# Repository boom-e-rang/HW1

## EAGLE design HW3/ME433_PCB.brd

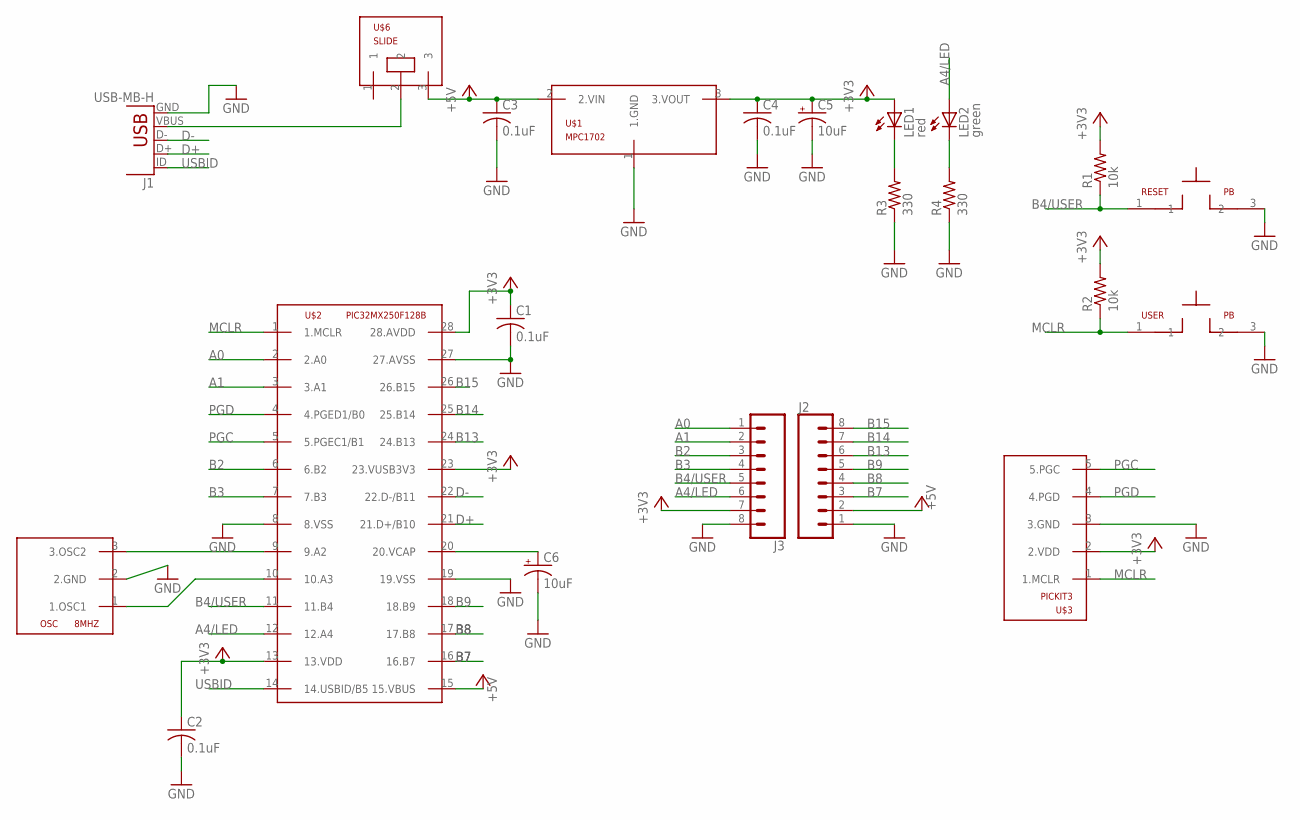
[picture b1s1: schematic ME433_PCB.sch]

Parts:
8MHZ: OSC
C1, C2, C3, C4: 0.1uF; C025-025X050
C5, C6: 10uF; B45181B
J1: USB-MB-H
J2, J3: CONN_08"; 1X08
LED1: red; LED3MM
LED2: green; LED3MM
R1, R2: 10k; 0207/10
R3, R4: 330; 0207/10
RESET: PB
U$1: MPC1702; TO92
U$2: PIC32MX250F128B; DIL28-3
U$3: PICKIT3; 1X05
U$6: SLIDE
USER: PB

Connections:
+3V3: C1.1, C2.1, C4.1, C5.+, J3.7, LED1.A, R1.2, R2.2, U$1.3 (3.VOUT), U$2.13 (13.VDD), U$2.23 (23.VUSB3V3), U$2.28 (28.AVDD), U$3.2 (2.VDD)
+5V: C3.1, J2.2, U$1.2 (2.VIN), U$2.15 (15.VBUS), U$6.3
A0: J3.1, U$2.2 (2.A0)
A1: J3.2, U$2.3 (3.A1)
A4/LED: J3.6, LED2.A, U$2.12 (12.A4)
B2: J3.3, U$2.6 (6.B2)
B3: J3.4, U$2.7 (7.B3)
B4/USER: J3.5, R1.1, RESET.1, U$2.11 (11.B4)
B7: J2.3, U$2.16 (16.B7)
B8: J2.4, U$2.17 (17.B8)
B9: J2.5, U$2.18 (18.B9)
B13: J2.6, U$2.24 (24.B13)
B14: J2.7, U$2.25 (25.B14)
B15: J2.8, U$2.26 (26.B15)
D+: J1.D+, U$2.21 (21.D+/B10)
D-: J1.D-, U$2.22 (22.D-/B11)
GND: 8MHZ.2 (2.GND), C1.2, C2.2, C3.2, C4.2, C5.-, C6.-, J1.GND, J2.1, J3.8, R3.1, R4.1, RESET.3 (2), U$1.1 (1.GND), U$2.8 (8.VSS), U$2.19 (19.VSS), U$2.27 (27.AVSS), U$3.3 (3.GND), USER.3 (2)
MCLR: R2.1, U$2.1 (1.MCLR), U$3.1 (1.MCLR), USER.1
unnamed: J1.VBUS, U$6.2
unnamed: 8MHZ.3 (3.OSC2), U$2.9 (9.A2)
unnamed: LED1.K (C), R3.2
unnamed: LED2.K (C), R4.2
unnamed: C6.+, U$2.20 (20.VCAP)
unnamed: 8MHZ.1 (1.OSC1), U$2.10 (10.A3)
PGC: U$2.5 (5.PGEC1/B1), U$3.5 (5.PGC)
PGD: U$2.4 (4.PGED1/B0), U$3.4 (4.PGD)
USBID: J1.ID, U$2.14 (14.USBID/B5)

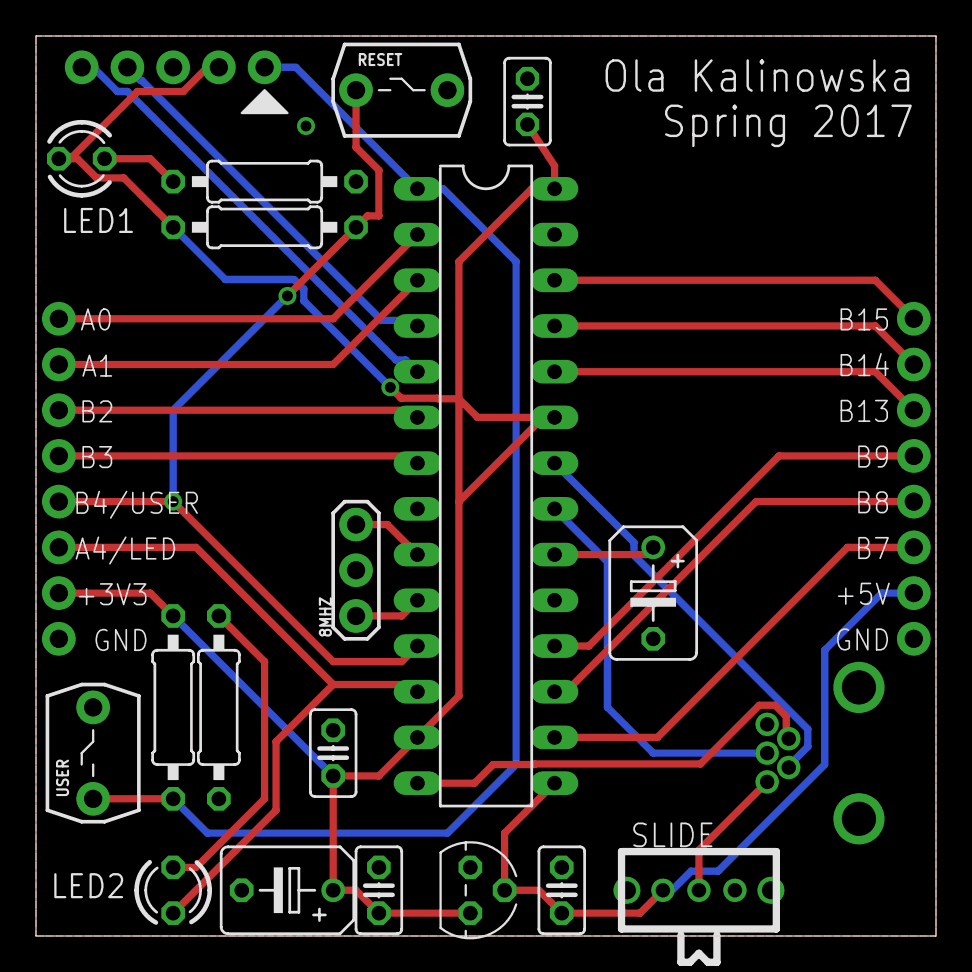
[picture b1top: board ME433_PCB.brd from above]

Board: 2 copper layers, 50.0 x 50.0 mm, 22 parts (0 on the bottom side), 27 nets.

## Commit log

2017-03-28 Added PDF
2017-03-29 HW1 photos
2017-03-29 New projects, pragmas set.
2017-03-29 Add pushbutton code
2017-03-30 Video
2017-04-07 Completed schematic
2017-04-07 Completed board
2017-04-07 GERBER files
2017-04-07 GERBER fixed slid screen
2017-04-10 HW4 continued
2017-04-11 working HW4 code
2017-04-11 HW5 continued
2017-04-12 circuit schematic
2017-04-12 HW5 complete
2017-04-20 harmony
2017-04-20 HW6 continued
2017-04-21 hw6 done!
2017-04-22 HW7 continued
2017-04-25 HW7 complete
2017-04-26 HW8 - it works!
2017-04-26 HW8 complete
2017-04-26 HW9 recognizes r
2017-04-26 HW9 continued
2017-04-27 HW9 complete
2017-04-27 HW9 video
2017-05-03 HW10
2017-05-03 HW11
2017-05-03 HW11 continued
2017-05-07 stuff
2017-05-07 HW12 complete
2017-05-11 HW13 complete
2017-05-11 HW10 update
2017-05-11 HW10 matlab code
2017-05-12 HW14 printing arrays to screen!
2017-05-13 HW14 app (no usb yet)
2017-05-18 HW14 complete
2017-05-22 HW CADing
2017-06-08 final project working
2017-06-08 TechCup alterations
